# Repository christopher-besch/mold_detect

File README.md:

# mold_detect

Warn residents of mold-friendly atmosphere and log opened windows.

This project is being developed in AVR_C on an Atmega328p.
It provides:
- Temperature, Humidity Logging (every minute with flash storage for two years)
- LED warning to motivate the opening of windows or turnign on of heaters
- Serial terminal via USB-C
- ~5uA power consumption at 3V battery power

The PCB is designed in KiCad and manufactured by Aisler.

# Parts
- [TPL5010](https://www.digikey.de/de/products/detail/texas-instruments/TPL5010DDCR/5119105)
- [2 AAA Battery pack](https://www.digikey.de/de/products/detail/keystone-electronics/2468/303817)
- [SHT30](https://www.digikey.de/de/products/detail/sensirion-ag/SHT30-DIS-B2-5KS/5872250)
- [W25Q128JVSIQ](https://www.digikey.de/de/products/detail/winbond-electronics/W25Q128JVSIQ-TR/5803944)
- [FT230XS](https://www.digikey.de/en/products/detail/ftdi-future-technology-devices-international-ltd/FT230XS-R/3029141)
- [USB4105](https://www.digikey.de/en/products/detail/gct/USB4105-GF-A/11198441)

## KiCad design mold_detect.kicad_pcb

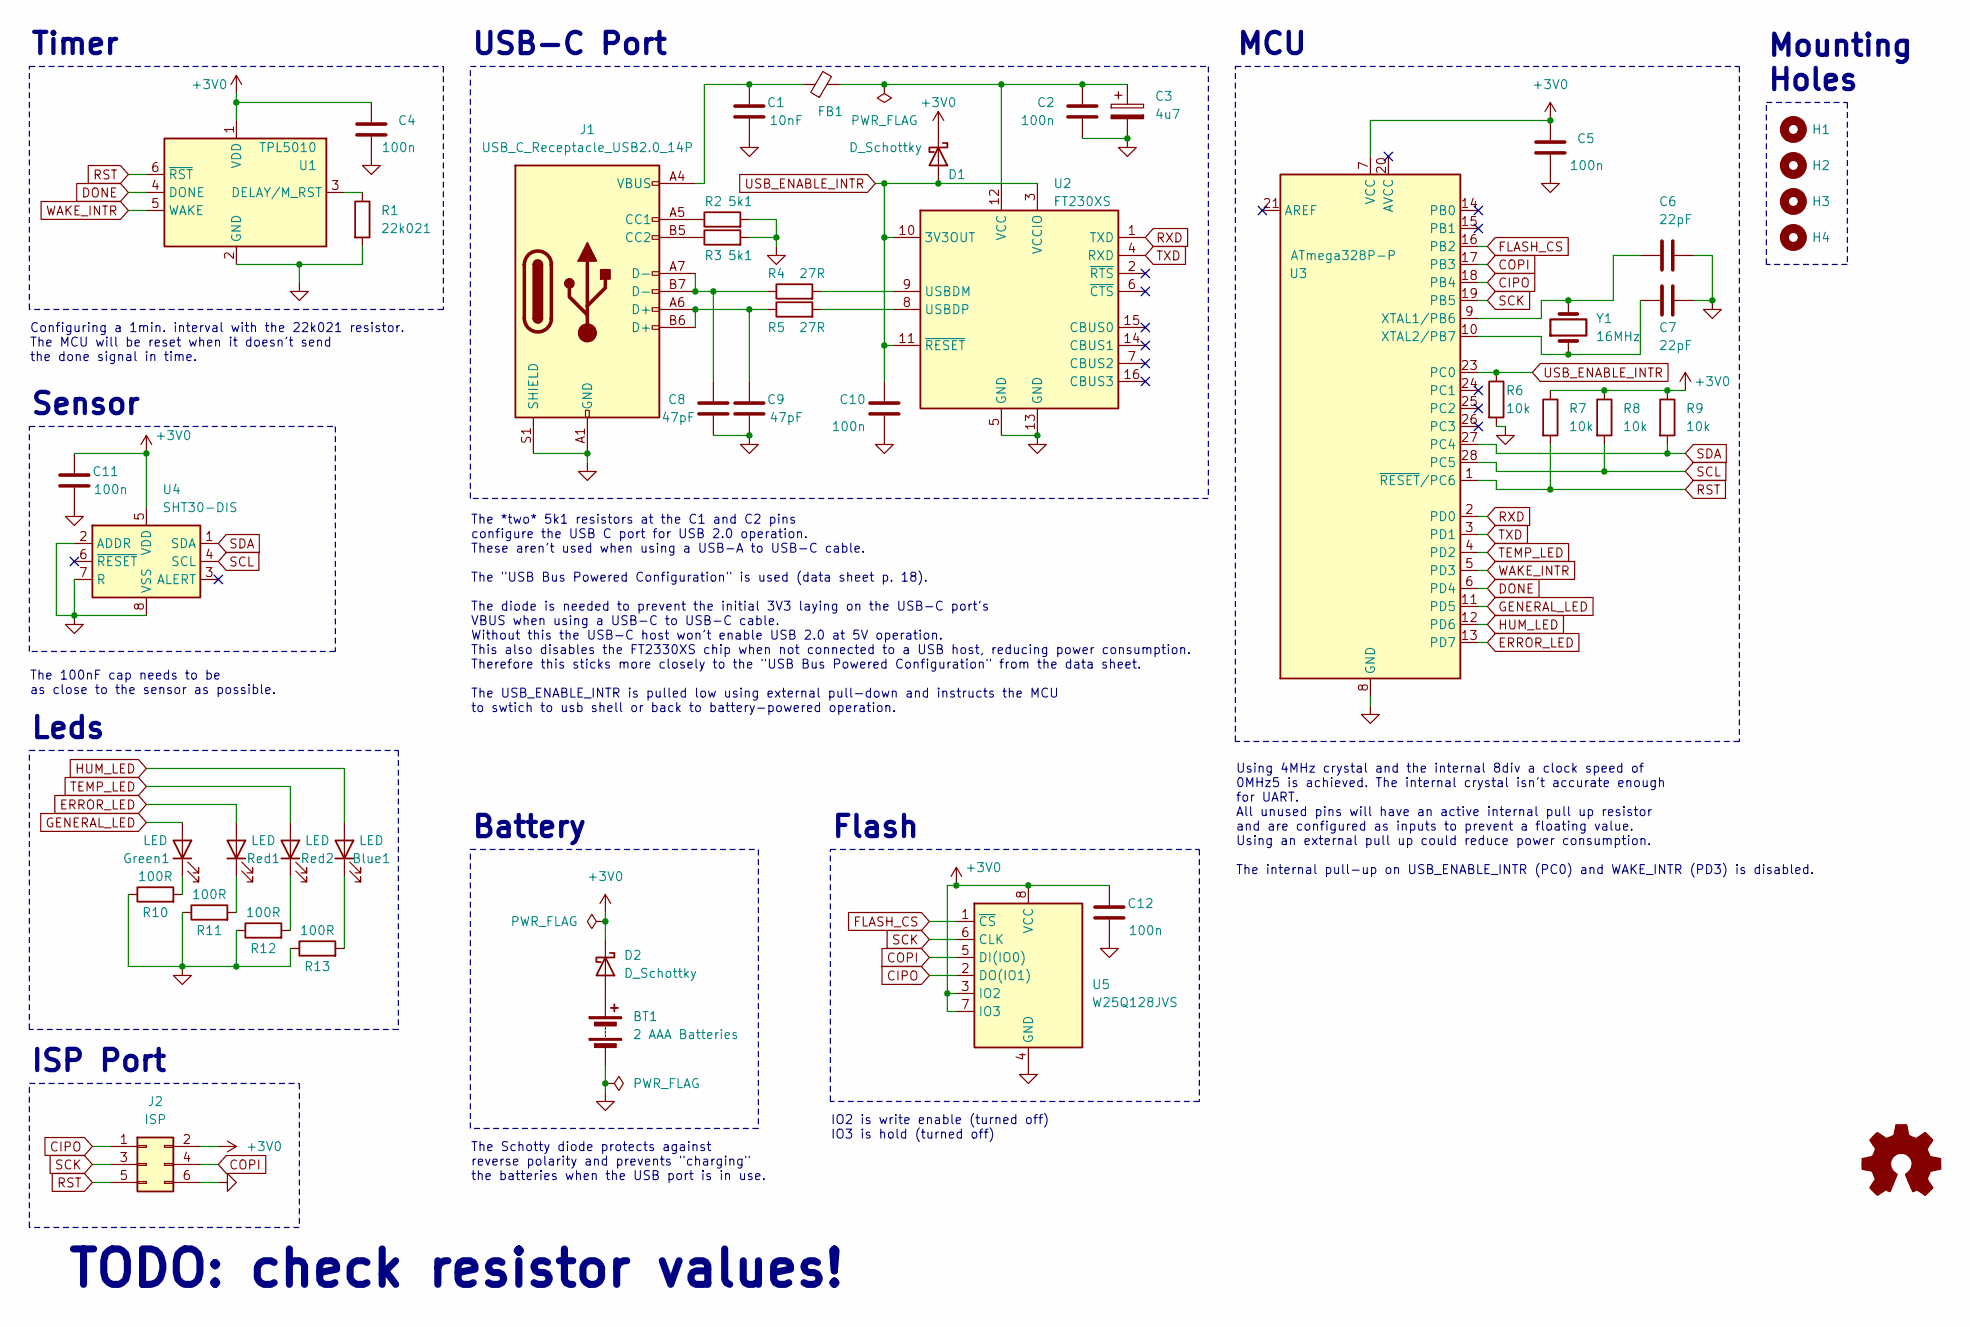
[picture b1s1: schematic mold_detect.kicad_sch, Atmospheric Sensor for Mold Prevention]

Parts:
BT1: 2 AAA Batteries; BatteryHolder_Keystone_2468_2xAAA
Blue1: LED; LED_D3.0mm
C1: 10nF; C_0603_1608Metric_Pad1.08x0.95mm_HandSolder
C2, C4, C5, C10, C11, C12: 100n; C_0603_1608Metric_Pad1.08x0.95mm_HandSolder
C3: 4u7; CP_Radial_D5.0mm_P2.00mm
C6, C7: 22pF; C_0603_1608Metric_Pad1.08x0.95mm_HandSolder
C8, C9: 47pF; C_0603_1608Metric_Pad1.08x0.95mm_HandSolder
D1, D2: D_Schottky; D_SOD-323_HandSoldering
FB1: C_0603_1608Metric_Pad1.08x0.95mm_HandSolder
Green1: LED; LED_D3.0mm
H1, H2, H3, H4: MountingHole_3.2mm_M3
J1: USB_C_Receptacle_USB2.0_14P; USB_C_Receptacle_GCT_USB4105-xx-A_16P_TopMnt_Horizontal
J2: ISP; IDC-Header_2x03_P2.54mm_Vertical
R1: 22k021; R_0603_1608Metric_Pad0.98x0.95mm_HandSolder
R2, R3: 5k1; R_0603_1608Metric_Pad0.98x0.95mm_HandSolder
R4, R5: 27R; R_0603_1608Metric_Pad0.98x0.95mm_HandSolder
R6, R7, R8, R9: 10k; R_0603_1608Metric_Pad0.98x0.95mm_HandSolder
R10, R11, R12, R13: 100R; R_0603_1608Metric_Pad0.98x0.95mm_HandSolder
Red1, Red2: LED; LED_D3.0mm
SYM1: github.com/christopher-besch/mold_detect; OSHW-Logo2_7.3x6mm_SilkScreen
U1: TPL5010; SOT-23-6
U2: FT230XS; SSOP-16_3.9x4.9mm_P0.635mm
U3: ATmega328P-P; DIP-28_W7.62mm
U4: SHT30-DIS; Sensirion_DFN-8-1EP_2.5x2.5mm_P0.5mm_EP1.1x1.7mm
U5: W25Q128JVS; SOIC-8_5.23x5.23mm_P1.27mm
Y1: 16MHz; Crystal_HC49-4H_Vertical

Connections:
+3V0: C4.2, C5.2, C11.2, C12.2, D1.1 (K), D2.1 (K), J2.2, R7.1, R8.1, R9.1, U1.1 (VDD), U3.7 (VCC), U4.5 (VDD), U5.3 (IO2), U5.7 (IO3), U5.8 (VCC)
CIPO: J2.1, U3.18 (PB4), U5.2 (DO(IO1))
COPI: J2.4, U3.17 (PB3), U5.5 (DI(IO0))
DONE: U1.4 (DONE), U3.6 (PD4)
ERROR_LED: Red1.2 (A), U3.13 (PD7)
FLASH_CS: U3.16 (PB2), U5.1 (~CS)
GENERAL_LED: Green1.2 (A), U3.11 (PD5)
GND: BT1.2 (-), C1.1, C2.1, C3.2, C4.1, C5.1, C6.1, C7.1, C8.1, C9.1, C10.1, C11.1, C12.1, J1.A1 (GND), J1.A12 (GND), J1.B1 (GND), J1.B12 (GND), J1.S1 (SHIELD), J2.6, R1.2, R2.2, R3.2, R6.2, R10.1, R11.1, R12.1, R13.1, U1.2 (GND), U2.5 (GND), U2.13 (GND), U3.8 (GND), U3.22 (GND), U4.2 (ADDR), U4.7 (R), U4.8 (VSS), U4.9 (VSS), U5.4 (GND)
HUM_LED: Blue1.2 (A), U3.12 (PD6)
unnamed: BT1.1 (+), D2.2 (A)
unnamed: Blue1.1 (K), R13.2
unnamed: C1.2, FB1.1, J1.A4 (VBUS), J1.A9 (VBUS), J1.B4 (VBUS), J1.B9 (VBUS)
unnamed: C8.2, J1.A7 (D-), J1.B7 (D-), R4.1
unnamed: C9.2, J1.A6 (D+), J1.B6 (D+), R5.1
unnamed: Green1.1 (K), R10.2
unnamed: J1.A5 (CC1), R2.1
unnamed: J1.B5 (CC2), R3.1
unnamed: R11.2, Red1.1 (K)
unnamed: R12.2, Red2.1 (K)
unnamed: R1.1, U1.3 (DELAY/M_RST)
unnamed: R4.2, U2.9 (USBDM)
unnamed: R5.2, U2.8 (USBDP)
unnamed: C2.2, C3.1, FB1.2, U2.12 (VCC)
unnamed: C6.2, U3.9 (XTAL1/PB6), Y1.2
unnamed: C7.2, U3.10 (XTAL2/PB7), Y1.1
RST: J2.5, R7.2, U1.6 (~RST), U3.1 (~RESET/PC6)
RXD: U2.1 (TXD), U3.2 (PD0)
SCK: J2.3, U3.19 (PB5), U5.6 (CLK)
SCL: R8.2, U3.28 (PC5), U4.4 (SCL)
SDA: R9.2, U3.27 (PC4), U4.1 (SDA)
TEMP_LED: Red2.2 (A), U3.4 (PD2)
TXD: U2.4 (RXD), U3.3 (PD1)
USB_ENABLE_INTR: C10.2, D1.2 (A), R6.1, U2.3 (VCCIO), U2.10 (3V3OUT), U2.11 (~RESET), U3.23 (PC0)
WAKE_INTR: U1.5 (WAKE), U3.5 (PD3)

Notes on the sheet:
ISP Port
Configuring a 1min. interval with the 22k021 resistor. The MCU will be reset when it doesn't send the done signal in time.
The 100nF cap needs to be as close to the sensor as possible.
TODO: check resistor values!
The *two* 5k1 resistors at the C1 and C2 pins configure the USB C port for USB 2.0 operation. These aren't used when using a USB-A to USB-C cable. The "USB Bus Powered Configuration" is used (data sheet p. 18). The diode is needed to prevent the initial 3V3 laying on the USB-C port's VBUS when usin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
Using 4MHz crystal and the internal 8div a clock speed of 0MHz5 is achieved. The internal crystal isn't accurate enough for UART. All unused pins will have an active internal pull up resistor and are configured as inputs to prevent a floating value. Using an external pull up could reduce power cons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
MCU
USB-C Port
Leds
IO2 is write enable (turned off) IO3 is hold (turned off)
Mounting Holes
The Schotty diode protects against reverse polarity and prevents "charging" the batteries when the USB port is in use.
Sensor
Flash
Timer
Battery

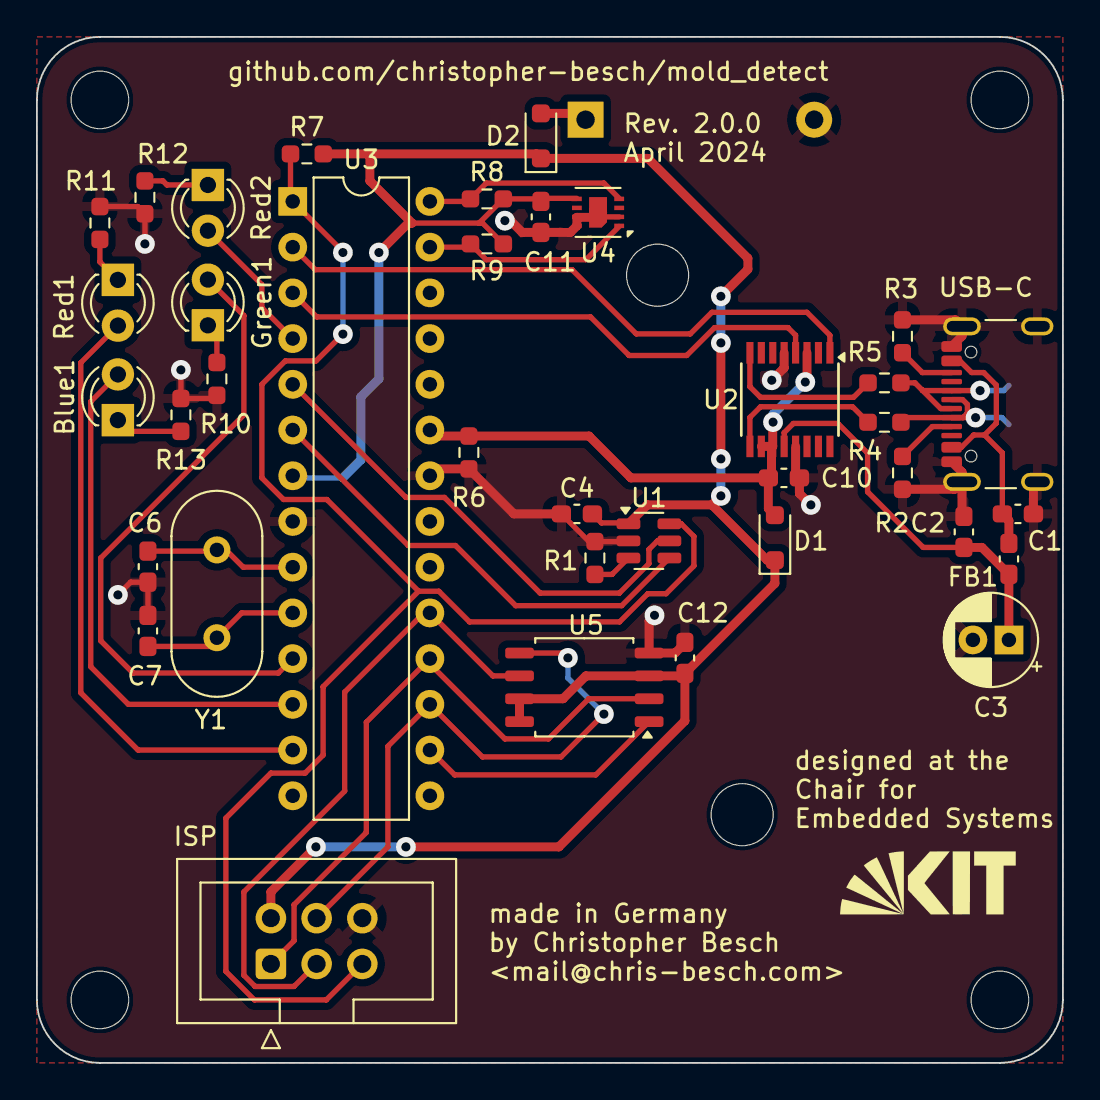
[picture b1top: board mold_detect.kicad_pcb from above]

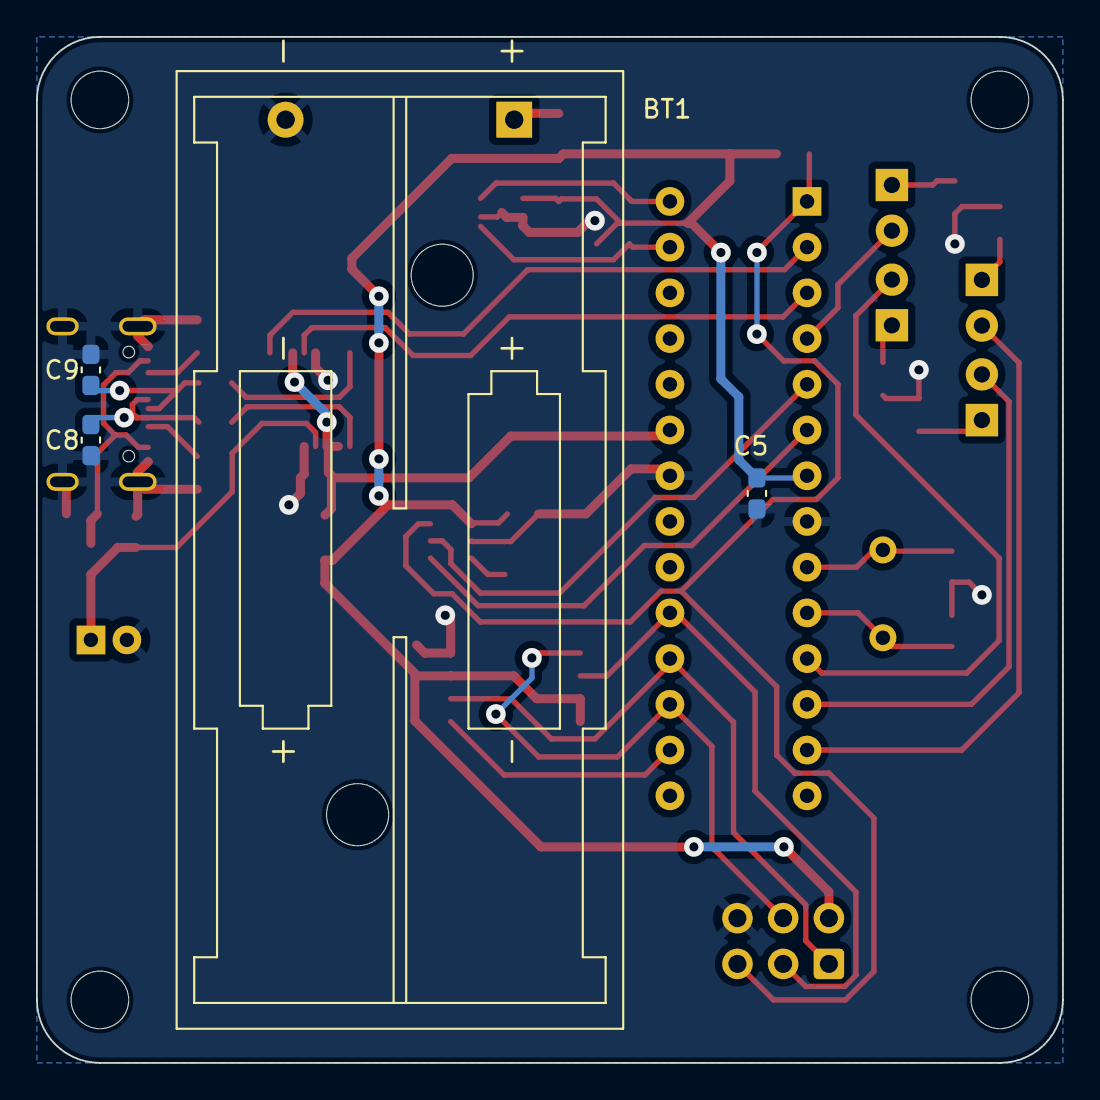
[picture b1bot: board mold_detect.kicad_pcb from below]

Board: 2 copper layers, 57.0 x 57.0 mm, 45 parts (4 on the bottom side), 34 nets.

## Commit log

2024-01-08 added data sheets
2024-01-08 added gitignore
2024-01-08 updated gitignore
2024-01-08 added ces reference; moved sensor to bottom
2024-01-08 better clearances
2024-01-08 added new gerber files
2024-01-09 removed isp; added uart; added flash
2024-01-15 added usb c port
2024-01-15 added readme
2024-01-22 changed usb-c port to match "USB Bus Powered Configuration" from p. 18
2024-01-30 added Makefile
2024-01-31 added external oscillator
2024-04-08 the spi flash chip works
2024-04-10 temp/hum sensor works!
2024-04-10 tpl5010 works!
2024-04-11 updated footprints; started layout
2024-04-11 updated PCB design
2024-04-17 added blender
2024-04-18 first casign design done
2024-04-18 added temp pdf
2024-04-18 added stl files
2024-04-18 added battery holder to 3d print
2024-04-18 before removing gnd connections
2024-04-18 ready to order pcb
2024-05-03 Added .PHONY to Makefile
    Thx Marwin!
2024-05-04 added structs for flash
2024-05-05 added error handling
2024-05-05 implemented simple terminal
2024-05-05 moved makefile into build dir
2024-05-05 using macros for pin names for interrupts
2024-05-05 implemented usb mode detection
2024-05-05 added null parameter checks
2024-05-06 fixed avr-size in Makefile and fixed should_measure = 1
2024-05-06 experimenting with flash
2024-05-06 binary search works
2024-05-07 feat: implemented flash erase
2024-06-07 feat: added atmosphere_bad and error flag; created constructors for flash blocks
2024-06-07 feat: added check after binary search
2024-06-07 feat: implemented flash readout
    This also fixes calling `flash_write_data` with a pointer pointer
    instead of a straight pointer.
    closes #3
2024-06-07 feat: added assert macro
    closes #5
2024-06-07 feat: added commit hash to version
    closes #7
2024-06-08 feat: using floats in json ouput; increase baud rate
2024-06-08 feat: implemented pretty kit logo
2024-06-08 feat: implemented timstamp system
    closes #4
2024-06-08 fix: small grammar fixes and comments
2024-06-08 fix: better function names
2024-06-08 feat: split uart functions into uart and print
2024-06-08 feat: attempting 20 measurements now
2024-06-09 feat: proper clock speed calculation
    This fixes the i2c measurement errors by reducing the i2c speed.
    This also sends an i2c stop condition after an i2c failure.
2024-06-09 fix: fixed 256 div factor value
2024-06-09 feat: added cppcheck
2024-06-09 feat: implemented flash power down
    closes #1
2024-06-10 fix: proper errors in measurement
    closes #9
2024-06-10 feat: added clock speeds to version display
2024-06-10 fix: fixed measure error state
2024-06-11 feat(case): using nut for battery
    closes #11
2025-03-20 Create LICENSE
2025-12-25 Create CNAME
